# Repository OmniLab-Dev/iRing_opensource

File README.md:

# iRing

Hardware and firmware for the iRing research prototype.

- [Firmware](firmware/iRing_OS/README.md): nRF52832 Arduino application, OLED UI,
  capacitive controls, BLE media keys, and optical heart-rate/SpO₂ acquisition.
- `pcb/`: PCB layout and schematic files.
- `3d/`: reserved for enclosure and mechanical design files.

Start with the [firmware build guide](firmware/iRing_OS/README.md) for board
connections, dependencies, controls, and BLE commands. The BLE device name is
`VisRing` for compatibility with existing pairings and companion software.

Third-party files retain their original notices; see [THIRD_PARTY.md](THIRD_PARTY.md).

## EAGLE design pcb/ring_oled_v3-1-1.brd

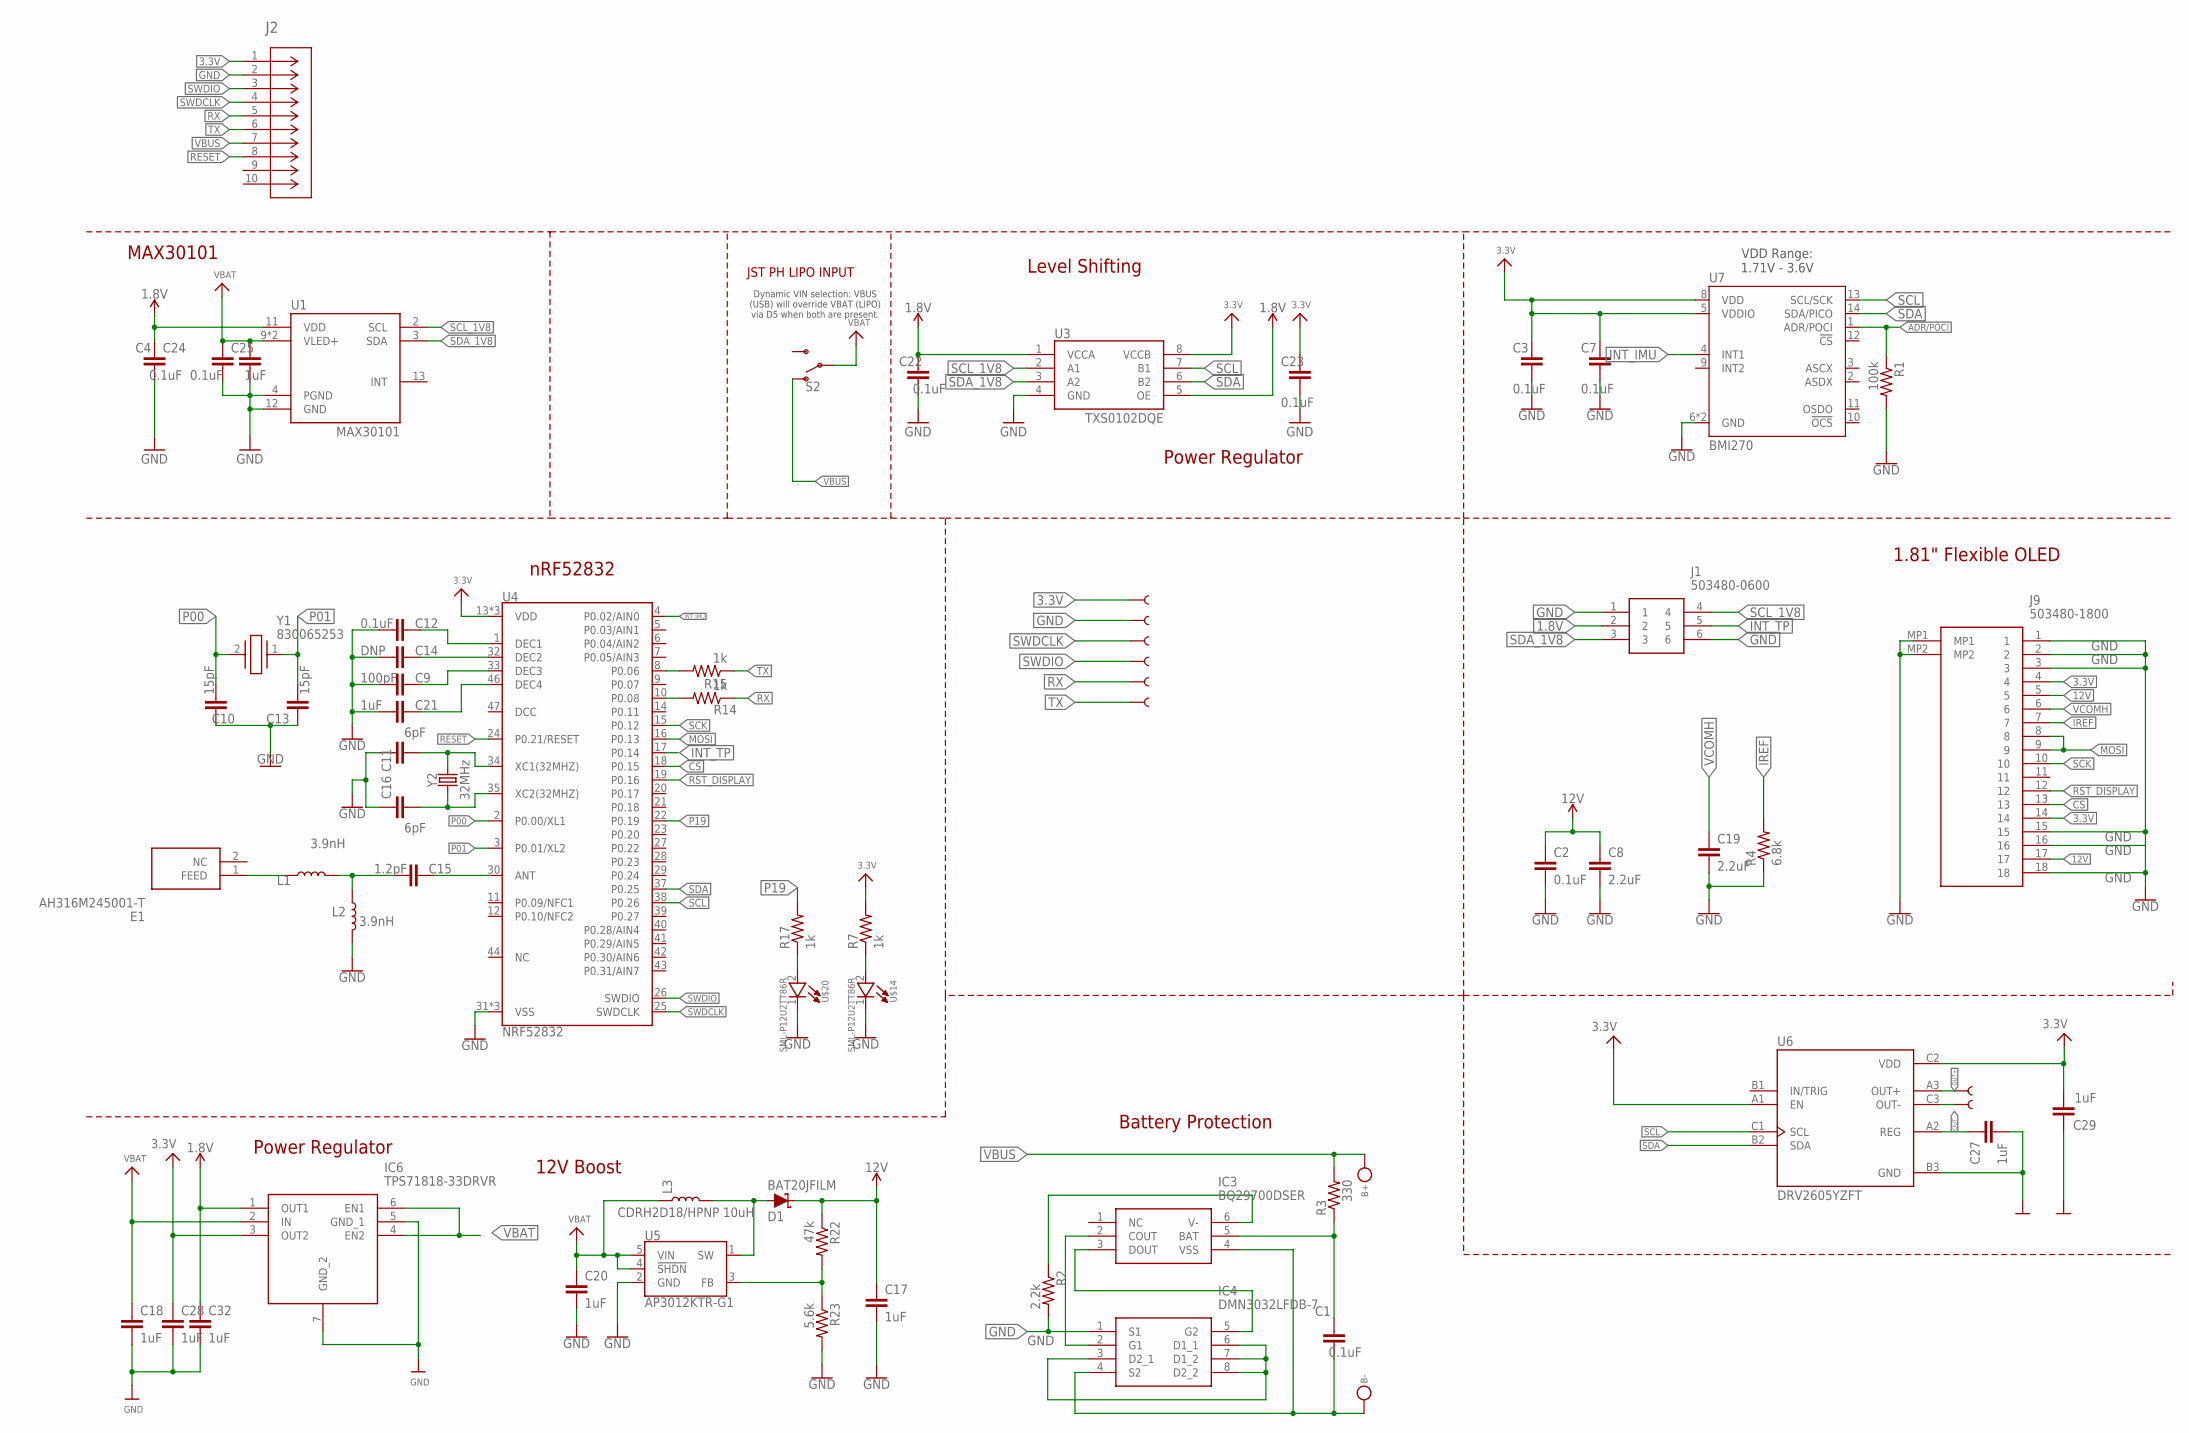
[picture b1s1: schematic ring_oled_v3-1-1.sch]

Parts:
B+: TESTPOINTROUND2MM; TESTPOINT_ROUND_2MM
B-: TESTPOINTROUND2MM; TESTPOINT_ROUND_2MM
C1, C3, C4, C7, C12, C22, C23, C24: 0.1uF; C0201
C2: 0.1uF; SPARKFUN-CAPACITORS_0402
C8, C19: 2.2uF; SPARKFUN-CAPACITORS_0402
C9: 100pF; C0201
C10, C13: 15pF; C0201
C11, C16: 6pF; C0201
C14: DNP; C0201
C15: 1.2pF; C0201
C17, C20: 1uF; SPARKFUN-CAPACITORS_0402
C18, C21, C25, C27, C28, C29, C32: 1uF; C0201
D1: BAT20JFILM; SOD-323
E1: AH316M245001-T; ANTC3216X60N
IC3: BQ29700DSER; SON50P150X150X80-6N
IC4: DMN3032LFDB-7; DMP1046UFDB7
IC6: TPS71818-33DRVR; SON65P200X200X80-7N
J1: 503480-0600
J2: 5050701022; CONN_505070-1022_MOL
J9: 503480-1800; 5034801800
L1, L2: 3.9nH; CAPC1005X55N
L3: CDRH2D18/HPNP 10uH; INDUCTOR_4.7UH
R1: 100k; R0201
R2: 2.2k; R0201
R3: 330; R0201
R4: 6.8k; R0201
R7, R14, R15, R17: 1k; R0201
R22: 47k; SPARKFUN-RESISTORS_0603
R23: 5.6k; SPARKFUN-RESISTORS_0603
S2: SWITCH-SPDT-SMD-RIGHT-ANGLE; SWITCH_SPST_SMD_A
U1: MAX30101; MAX30100
U3: TXS0102DQE; DQE(R-PX2SON-N8)
U4: NRF52832; QFN48-6X6MM
U5: AP3012KTR-G1; SOT23-5
U6: DRV2605YZFT; IC_DRV2604YZFT
U7: BMI270
U$14, U$20: SML-P12U2TT86R; DIODFN100X60X43-2N
VBUS1, VBUS2, VBUS3, VBUS4, VBUS5, VBUS6, VBUS7, VBUS8: TEST-POINT3; PAD.03X.03
Y1: 830065253
Y2: 32MHz; CRYSTAL-SMD-2.0X1.6MM

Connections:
1.8V: C4.1, C22.1, C32.1, IC6.1 (OUT1), J1.2, U1.11 (VDD), U3.1 (VCCA), U3.5 (OE)
3.3V: C3.1, C7.1, C23.1, C28.1, C29.2, IC6.3 (OUT2), J2.1, J9.4, J9.14, R7.2, U3.8 (VCCB), U4.13 (VDD), U4.36 (VDD), U4.48 (VDD), U6.A1 (EN), U6.C2 (VDD), U7.5 (VDDIO), U7.8 (VDD), VBUS1.P$1
12V: C2.1, C8.1, C17.1, D1.C, J9.5, J9.17, R22.1
ADR/POCI: R1.1, U7.1 (ADR/POCI)
CS: J9.13, U4.18 (P0.15)
DEC1: C12.1, U4.1 (DEC1)
DEC2: C14.1, U4.32 (DEC2)
DEC3: C9.1, U4.33 (DEC3)
DEC4: C21.1, U4.46 (DEC4)
GND: C2.2, C3.2, C4.2, C7.2, C8.2, C9.2, C10.1, C11.1, C12.2, C13.1, C14.2, C16.1, C17.2, C18.2, C19.2, C20.2, C21.2, C22.2, C23.2, C24.2, C25.2, C27.2, C28.2, C29.1, C32.2, IC4.1 (S1), IC6.5 (GND_1), IC6.7 (GND_2), J1.1, J1.6, J2.2, J9.1, J9.2, J9.3, J9.15, J9.16, J9.18, J9.MP1, J9.MP2, L2.2, R1.2, R2.2, R4.1, R23.2, U1.4 (PGND), U1.12 (GND), U3.4 (GND), U4.31 (VSS), U4.45 (VSS), U4.EP (VSS), U5.2 (GND), U6.B3 (GND), U7.6 (GND), U7.7 (GND), U$14.1 (C), U$20.1 (C), VBUS2.P$1
INT_IMU: U4.4 (P0.02/AIN0), U7.4 (INT1)
INT_TP: J1.5, U4.17 (P0.14)
IREF: J9.7, R4.2
MOSI: J9.8, J9.9, U4.16 (P0.13)
unnamed: IC4.3 (D2_1), IC4.6 (D1_1), IC4.7 (D1_2), IC4.8 (D2_2)
unnamed: IC3.2 (COUT), IC4.2 (G1)
unnamed: IC3.3 (DOUT), IC4.5 (G2)
unnamed: C15.2, L1.2, L2.1
unnamed: IC3.6 (V-), R2.1
unnamed: R7.1, U$14.2 (A)
unnamed: B-.P$1, C1.2, IC3.4 (VSS), IC4.4 (S2)
unnamed: E1.1 (FEED), L1.1
unnamed: C15.1, U4.30 (ANT)
unnamed: C1.1, IC3.5 (BAT), R3.1
unnamed: R15.2, U4.8 (P0.06)
unnamed: R14.2, U4.10 (P0.08)
unnamed: D1.A, L3.P$2 (2), U5.1 (SW)
unnamed: R22.2, R23.1, U5.3 (FB)
unnamed: C27.1, U6.A2 (REG)
unnamed: R17.1, U$20.2 (A)
OUT+: U6.A3 (OUT+), VBUS3.P$1
OUT-: U6.C3 (OUT-), VBUS4.P$1
P00: C10.2, U4.2 (P0.00/XL1), Y1.2 (CRYSTAL_2)
P01: C13.2, U4.3 (P0.01/XL2), Y1.1 (CRYSTAL_1)
P19: R17.2, U4.22 (P0.19)
RESET: J2.8, U4.24 (P0.21/RESET)
RST_DISPLAY: J9.12, U4.19 (P0.16)
RX: J2.5, R14.1, VBUS7.P$1
SCK: J9.10, U4.15 (P0.12)
SCL: U3.7 (B1), U4.38 (P0.26), U6.C1 (SCL), U7.13 (SCL/SCK)
SCL_1V8: J1.4, U1.2 (SCL), U3.2 (A1)
SDA: U3.6 (B2), U4.37 (P0.25), U6.B2 (SDA), U7.14 (SDA/PICO)
SDA_1V8: J1.3, U1.3 (SDA), U3.3 (A2)
SWDCLK: J2.4, U4.25 (SWDCLK), VBUS5.P$1
SWDIO: J2.3, U4.26 (SWDIO), VBUS6.P$1
TX: J2.6, R15.1, VBUS8.P$1
VBAT: C18.1, C20.1, C24.1, C25.1, IC6.2 (IN), IC6.4 (EN2), IC6.6 (EN1), L3.P$1 (1), S2.2, U1.9 (VLED+), U1.10 (VLED+), U5.4 (!SHDN!), U5.5 (VIN)
VBUS: B+.P$1, J2.7, R3.2, S2.1 (O)
VCOMH: C19.1, J9.6
XC1: C11.2, U4.34 (XC1(32MHZ)), Y2.3 (2)
XC2: C16.2, U4.35 (XC2(32MHZ)), Y2.1

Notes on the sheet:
MAX30101
1.81" Flexible OLED
12V Boost
Level Shifting
VDD Range: 1.71V - 3.6V
Power Regulator
nRF52832
Battery Protection
JST PH LIPO INPUT
Dynamic VIN selection: VBUS (USB) will override VBAT (LIPO) via D5 when both are present.

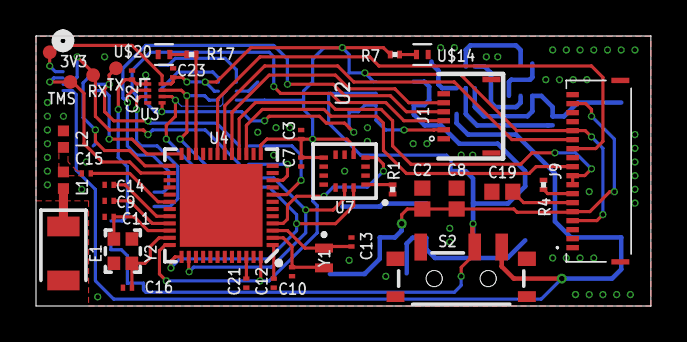
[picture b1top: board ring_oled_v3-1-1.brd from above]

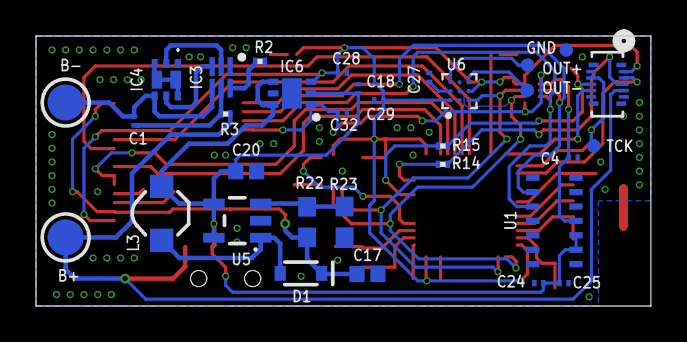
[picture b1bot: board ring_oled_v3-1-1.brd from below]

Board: 2 copper layers, 34.2 x 15.0 mm, 69 parts (32 on the bottom side), 51 nets.

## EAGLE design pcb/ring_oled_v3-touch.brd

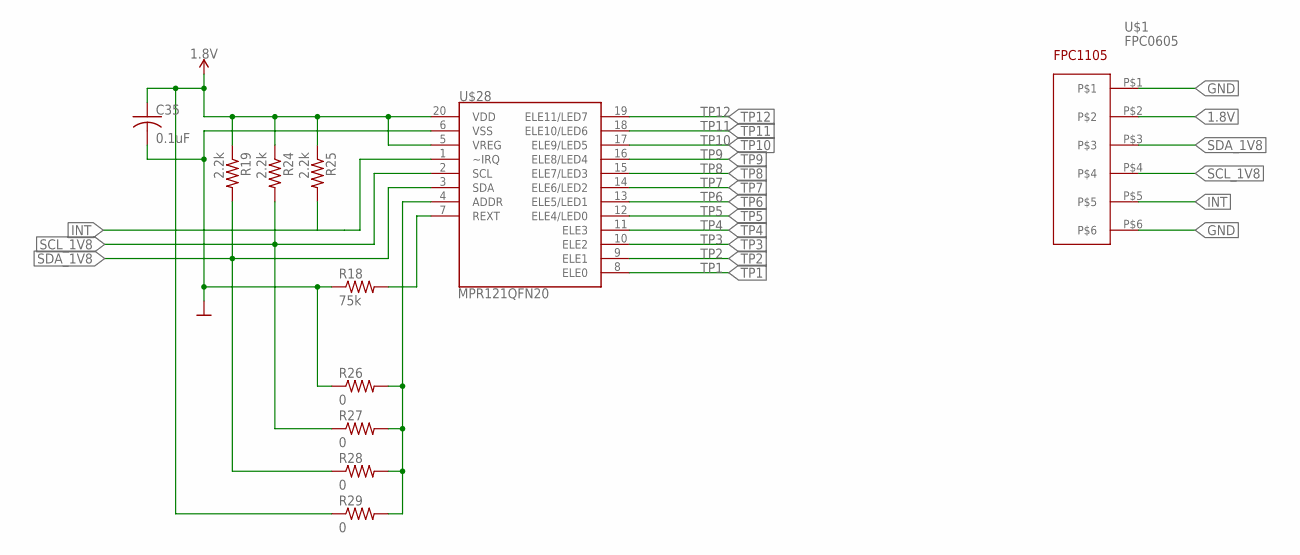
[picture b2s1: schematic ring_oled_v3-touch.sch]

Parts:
C35: 0.1uF; C0402
R18: 75k; R0402
R19, R24, R25: 2.2k; R0402
R26, R27, R28, R29: 0; R0402
U$1: FPC0605
U$28: MPR121QFN20; QFN-20-0.4MM

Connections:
1.8V: C35.1, R19.1, R24.1, R25.1, R29.1, U$1.P$2, U$28.5 (VREG), U$28.20 (VDD)
GND: C35.2, R18.1, R26.1, U$1.P$1, U$1.P$6, U$28.6 (VSS)
INT: R25.2, U$1.P$5, U$28.1 (~IRQ)
unnamed: R18.2, U$28.7 (REXT)
unnamed: R26.2, R27.2, R28.2, R29.2, U$28.4 (ADDR)
SCL_1V8: R24.2, R27.1, U$1.P$4, U$28.2 (SCL)
SDA_1V8: R19.2, R28.1, U$1.P$3, U$28.3 (SDA)
TP1: U$28.8 (ELE0)
TP2: U$28.9 (ELE1)
TP3: U$28.10 (ELE2)
TP4: U$28.11 (ELE3)
TP5: U$28.12 (ELE4/LED0)
TP6: U$28.13 (ELE5/LED1)
TP7: U$28.14 (ELE6/LED2)
TP8: U$28.15 (ELE7/LED3)
TP9: U$28.16 (ELE8/LED4)
TP10: U$28.17 (ELE9/LED5)
TP11: U$28.18 (ELE10/LED6)
TP12: U$28.19 (ELE11/LED7)

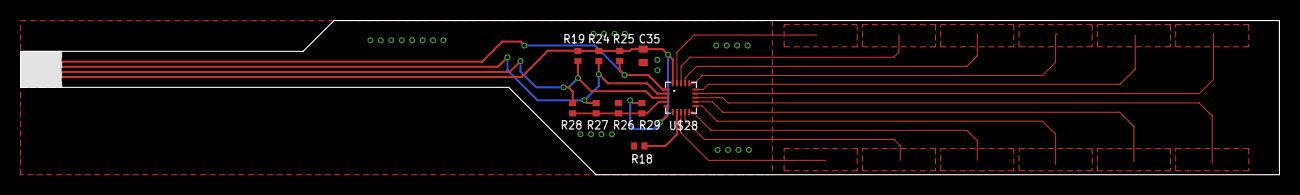
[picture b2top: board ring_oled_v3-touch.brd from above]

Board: 2 copper layers, 122.5 x 15.0 mm, 11 parts (0 on the bottom side), 7 nets.

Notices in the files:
parts and their libraries:
SparkFun-Connectors: Licensing: Creative Commons ShareAlike 4.0 International - https://creativecommons.org/licenses/by-sa/4.0
microbuilder: This work is placed in the public domain, and may be freely used for commercial and non-commercial work with the following conditions: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
